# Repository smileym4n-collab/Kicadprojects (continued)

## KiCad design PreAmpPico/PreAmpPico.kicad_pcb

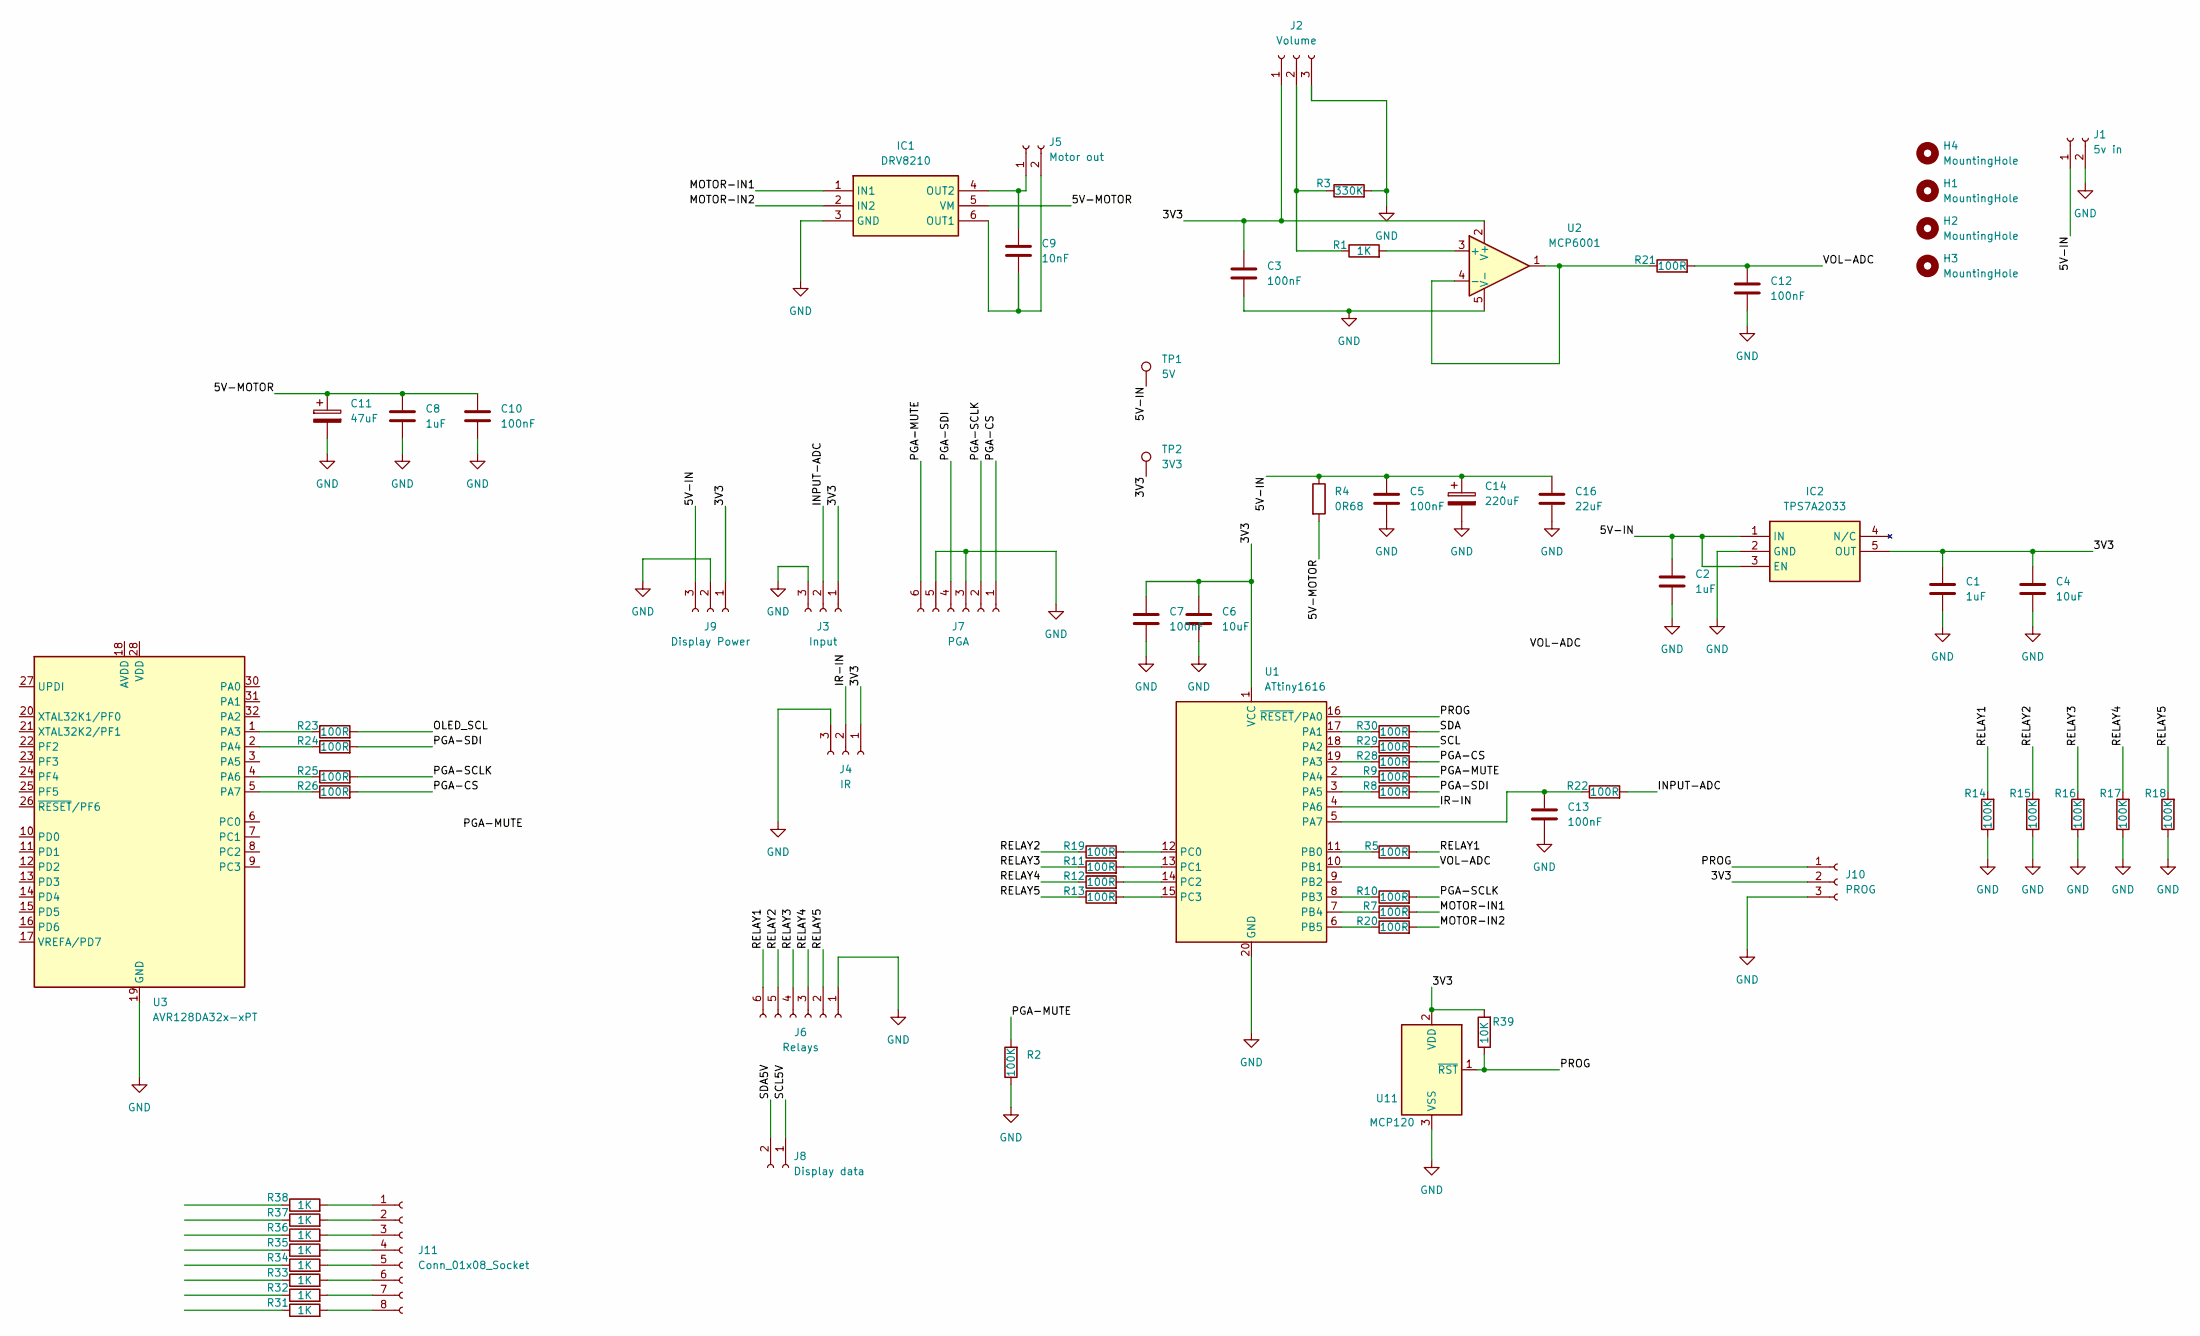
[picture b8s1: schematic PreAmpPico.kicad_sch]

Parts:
C1, C2, C8: 1uF; C_1206_3216Metric_Pad1.33x1.80mm_HandSolder
C3, C5, C7, C10, C12, C13: 100nF; C_1206_3216Metric_Pad1.33x1.80mm_HandSolder
C4, C6: 10uF; C_1206_3216Metric_Pad1.33x1.80mm_HandSolder
C9: 10nF; C_0805_2012Metric_Pad1.18x1.45mm_HandSolder
C11: 47uF; CP_Radial_D6.3mm_P2.50mm
C14: 220uF; CP_Radial_D6.3mm_P2.50mm
C16: 22uF; C_1206_3216Metric_Pad1.33x1.80mm_HandSolder
H1, H2, H3, H4: MountingHole; MountingHole_4mm
IC1: DRV8210; Mouser Part Number 595-DRV8210DRLR
IC2: TPS7A2033; SOT95P280X145-5N; Mouser Part Number 595-TPS7A2033PDBVR
J1: 5v in; JST_XH_B2B-XH-A_1x02_P2.50mm_Vertical
J2: Volume; JST_XH_B3B-XH-A_1x03_P2.50mm_Vertical
J3: Input; JST_XH_B3B-XH-A_1x03_P2.50mm_Vertical
J4: IR; JST_XH_B3B-XH-A_1x03_P2.50mm_Vertical
J5: Motor out; JST_XA_B02B-XASK-1_1x02_P2.50mm_Vertical
J6: Relays; JST_XH_B6B-XH-A_1x06_P2.50mm_Vertical
J7: PGA; JST_XH_B6B-XH-A_1x06_P2.50mm_Vertical
J8: Display data; JST_XA_B02B-XASK-1_1x02_P2.50mm_Vertical
J9: Display Power; JST_XH_B3B-XH-A_1x03_P2.50mm_Vertical
J10: PROG; PinSocket_1x03_P2.54mm_Vertical
J11: Conn_01x08_Socket; PinHeader_1x08_P2.54mm_Vertical
R1, R31, R32, R33, R34, R35, R36, R37, R38: 1K; R_0805_2012Metric_Pad1.20x1.40mm_HandSolder
R2, R14, R15, R16, R17, R18: 100K; R_0805_2012Metric_Pad1.20x1.40mm_HandSolder
R3: 330K; R_0805_2012Metric_Pad1.20x1.40mm_HandSolder
R4: 0R68; R_1206_3216Metric_Pad1.30x1.75mm_HandSolder
R5, R7, R8, R9, R10, R11, R12, R13, R19, R20, R21, R22, R23, R24, R25, R26, R28, R29, R30: 100R; R_0805_2012Metric_Pad1.20x1.40mm_HandSolder
R39: 10K; R_0805_2012Metric_Pad1.20x1.40mm_HandSolder
TP1: 5V; TestPoint_Pad_2.0x2.0mm
TP2: 3V3; TestPoint_Pad_2.0x2.0mm
U1: ATtiny1616; SSOP-20_5.3x7.2mm_P0.65mm
U2: MCP6001; SOT-23-5
U3: AVR128DA32x-xPT; TQFP-32_7x7mm_P0.8mm
U11: MCP120; SOT-23

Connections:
/3V3: C1.1, C3.1, C4.1, C6.1, C7.1, IC2.5 (OUT), J2.1, J3.1, J4.1, J9.1, J10.2, R39.2, TP2.1 (1_1), U1.1 (VCC), U2.2 (V+), U11.2 (VDD)
/5V-IN: C2.1, C5.1, C14.1, C16.1, IC2.1 (IN), IC2.3 (EN), J1.1, J9.3, R4.1, TP1.1 (1_1)
/5V-MOTOR: C8.1, C10.1, C11.1, IC1.5 (VM), R4.2
/INPUT-ADC: J3.2, R22.2
/IR-IN: J4.2, U1.4 (PA6)
/MOTOR-IN1: IC1.1 (IN1), R7.2
/MOTOR-IN2: IC1.2 (IN2), R20.2
/PGA-CS: J7.1, R26.2, R28.2
/PGA-MUTE: J7.6, R2.2, R9.2
/PGA-SCLK: J7.2, R10.2, R25.2
/PGA-SDI: J7.4, R8.2, R24.2
/PROG: J10.1, R39.1, U1.16 (~RESET/PA0), U11.1 (~RST)
/RELAY1: J6.6, R5.2, R14.2
/RELAY2: J6.5, R15.2, R19.1
/RELAY3: J6.4, R11.1, R16.2
/RELAY4: J6.3, R12.1, R17.2
/RELAY5: J6.2, R13.1, R18.2
/SCL: R29.2
/SCL5V: J8.1
/SDA: R30.2
/SDA5V: J8.2
/VOL-ADC: C12.1, R21.2, U1.10 (PB1)
unnamed: C9.2, IC1.6 (OUT1), J5.2
unnamed: C9.1, IC1.4 (OUT2), J5.1
unnamed: J2.2, R1.1, R3.1
unnamed: J11.1, R38.2
unnamed: J11.2, R37.2
unnamed: J11.3, R36.2
unnamed: J11.4, R35.2
unnamed: J11.5, R34.2
unnamed: J11.6, R33.2
unnamed: J11.7, R32.2
unnamed: J11.8, R31.2
unnamed: R23.1, U3.1 (PA3)
unnamed: R24.1, U3.2 (PA4)
unnamed: R25.1, U3.4 (PA6)
unnamed: R26.1, U3.5 (PA7)
unnamed: R30.1, U1.17 (PA1)
unnamed: R29.1, U1.18 (PA2)
unnamed: R28.1, U1.19 (PA3)
unnamed: R9.1, U1.2 (PA4)
unnamed: R8.1, U1.3 (PA5)
unnamed: C13.1, R22.1, U1.5 (PA7)
unnamed: R5.1, U1.11 (PB0)
unnamed: R10.1, U1.8 (PB3)
unnamed: R7.1, U1.7 (PB4)
unnamed: R20.1, U1.6 (PB5)
unnamed: R19.2, U1.12 (PC0)
unnamed: R11.2, U1.13 (PC1)
unnamed: R12.2, U1.14 (PC2)
unnamed: R13.2, U1.15 (PC3)
unnamed: R1.2, U2.3 (+)
unnamed: R21.1, U2.1, U2.4 (-)

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
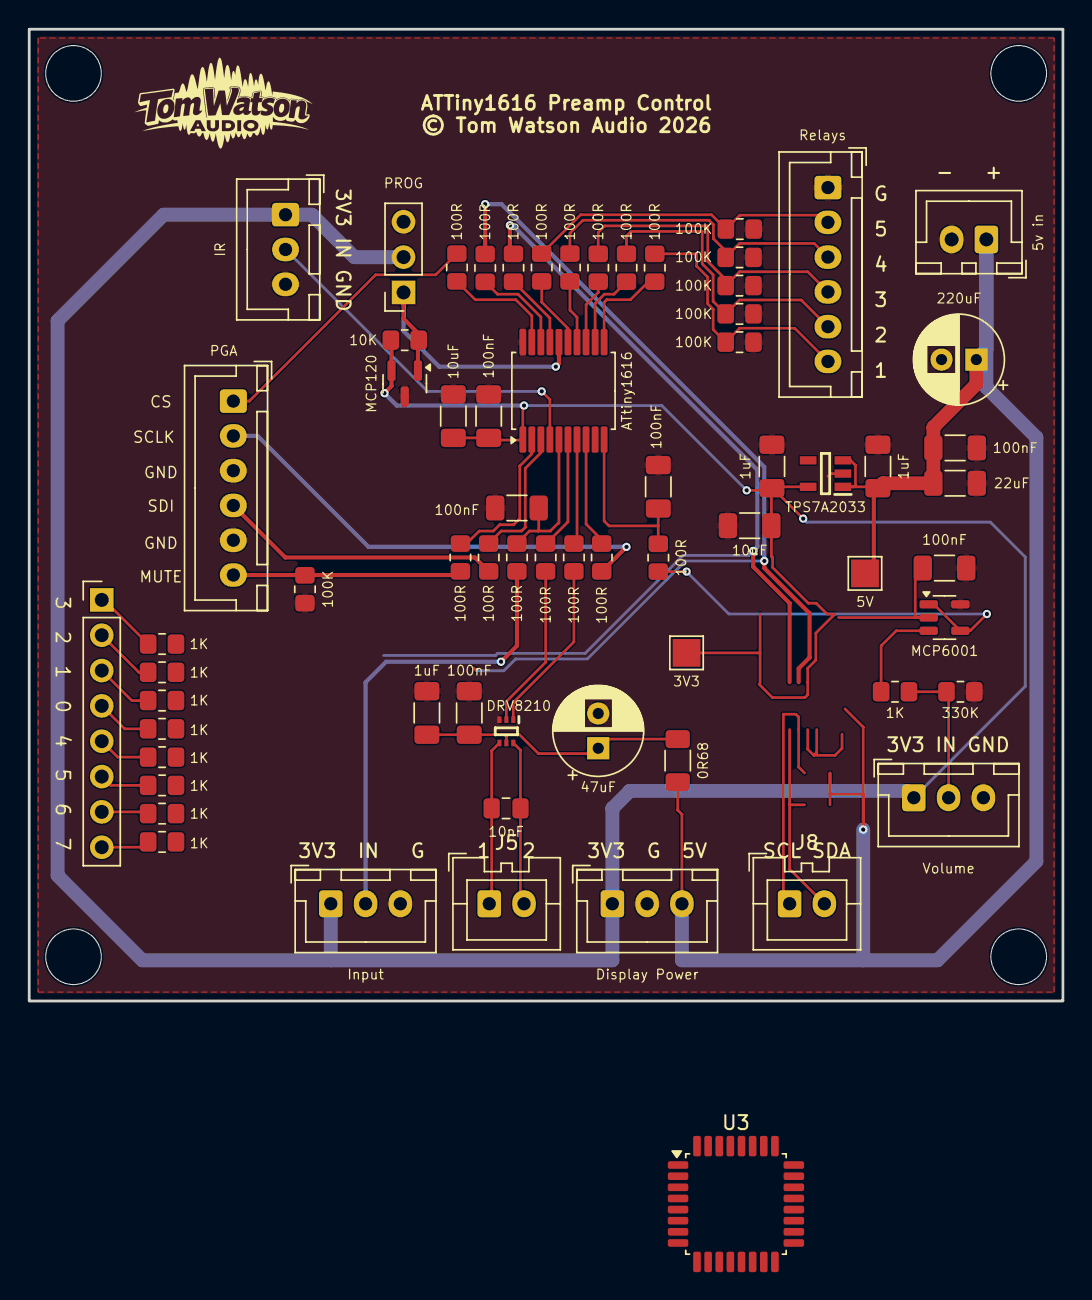
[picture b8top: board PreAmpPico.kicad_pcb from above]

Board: 2 copper layers, 74.3 x 69.9 mm, 71 parts (0 on the bottom side), 47 nets.

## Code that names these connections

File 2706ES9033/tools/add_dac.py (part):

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    W((px, RAIL), (px, py))
RC("C21", "10u", X0 - 38.1, RAIL + 3.81); gnd(X0 - 38.1, RAIL + 7.62)
pwrflag(X0 - 22.86, RAIL)
RC("C22", "100n", X0 - 27.94, RAIL + 3.81); gnd(X0 - 27.94, RAIL + 7.62)    # AVDD pin 1
RC("C23", "1u", X0 - 17.78, RAIL + 3.81); gnd(X0 - 17.78, RAIL + 7.62)      # AVDD pin 1
RC("C24", "1u", X0 + 17.78, RAIL + 3.81); gnd(X0 + 17.78, RAIL + 7.62)      # VCCA pin 4
RC("C25", "1u", X0 + 27.94, RAIL + 3.81); gnd(X0 + 27.94, RAIL + 7.62)      # AVCC_3V3 pin 9
RC("C26", "100n", X0 + 38.1, RAIL + 3.81); gnd(X0 + 38.1, RAIL + 7.62)      # AVCC_CP pin 17
RC("C27", "1u", X0 + 48.26, RAIL + 3.81); gnd(X0 + 48.26, RAIL + 7.62)      # AVCC_CP pin 17
T("Place at pins: C22,C23 -> pin 1 AVDD;  C24 -> pin 4 VCCA;  C25 -> pin 9 AVCC_3V3;  C26,C27 -> pin 17 AVCC_CP",
  X0 - 30.48, RAIL - 8.89, 1.27)

# ---------------- U2 left side: I2S, control, straps ----------------
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    px, py = P("U3", n)
    W((px, py), (px + 7.62, py))
    L(net, px + 7.62, py)
ncs.append(P("U3", "7"))                 # PA3 spare
# PA6: PCM2706 3V3 rail sense through R25
px, py = P("U3", "2")
sx = px + 12.7
W((px, py), (sx, py), (sx, py + 3.81))
RC("R25", "10k", sx, py + 7.62)
W((sx, py + 11.43), (sx, py + 13.97))
L("3V3", sx, py + 13.97, 270)
# PA7: DAC_EN with pull-down
px, py = P("U3", "3")
dx = px + 2.54
W((px, py), (dx, py), (dx, py + 3.81))
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RC("R24", "100k", dx, py + 7.62)
gnd(dx, py + 11.43)
T("CONTROL", AX - 45.72, AY - 33.02, 2.54, True)
T("U3 holds DAC_EN low until the PCM2706 3V3 rail is up and MCLK is stable,\nthen CHIP_EN high, wait 100 ms, clock setup at 0x98, then config at 0x90.\nPA6 senses the PCM2706 rail (3V3) via R25.  PA3 spare.",
  AX - 22.86, AY + 33.02, 1.27)
# I2C pull-ups
for ref, x, net in (("R22", AX + 25.4, "I2C_SDA"), ("R23", AX + 33.02, "I2C_SCL")):
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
